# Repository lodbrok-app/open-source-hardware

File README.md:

# open-source-hardware
Open-source components of the Lodbrok stack

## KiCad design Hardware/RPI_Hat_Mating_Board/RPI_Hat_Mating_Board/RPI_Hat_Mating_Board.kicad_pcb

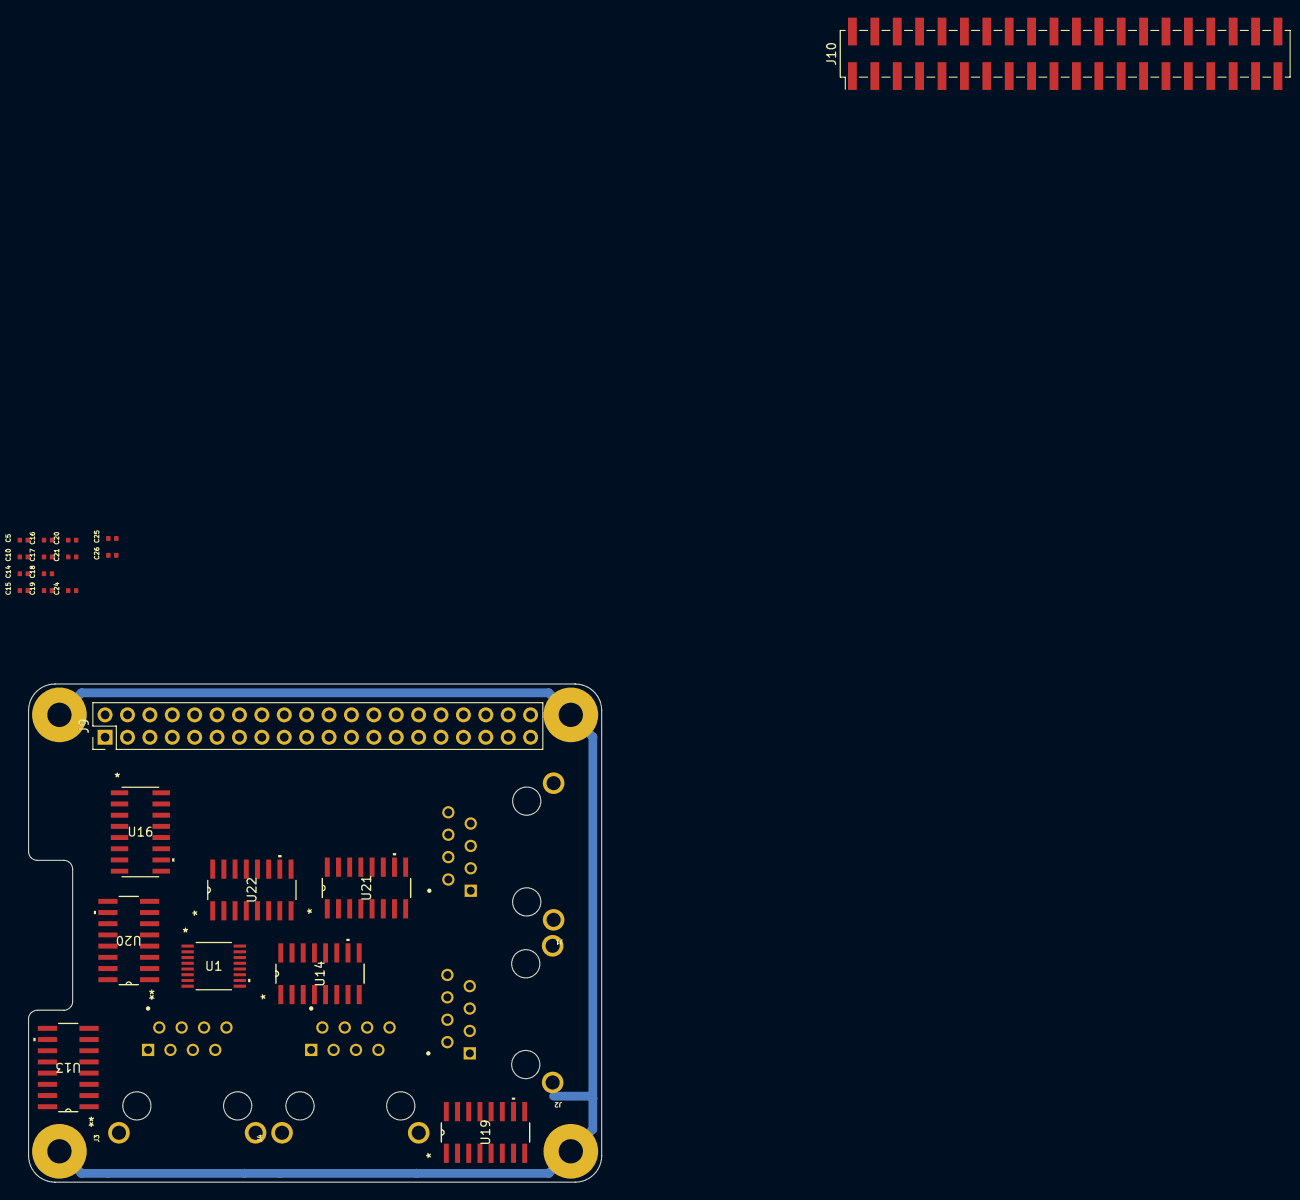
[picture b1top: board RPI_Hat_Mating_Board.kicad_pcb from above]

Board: 2 copper layers, 65.0 x 56.5 mm, 31 parts (0 on the bottom side), 48 nets.

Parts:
C5, C10, C14, C15, C16, C17, C18, C19, C20, C21, C24, C25, C26: Cap_0.1uF_10%_16V_0402; CAP_0402_0.6mm_Height
J1, J2, J3, J4: Conn_RJ45_Shielded_8p8c_RA_A-2004-2-4-LPS-N-R; A-2004-2-4-LPS-N-R
J9: Conn_02x20_Counter_Clockwise_MountingPin; PinHeader_2x20_P2.54mm_Vertical
J10: Conn_02x20_Counter_Clockwise_MountingPin; PinHeader_2x20_P2.54mm_Vertical_SMD
MP1, MP2, MP3, MP4: STAND_OFF_M3_2mm_NS_SMT; 9774020960
U1: TMUX1208PWR; PW_16_TEX
U13, U14: AM26LV32EIDR; D16
U16: 74HC137; SOIC16-N_MC_MCH
U19, U20, U21, U22: AM26LV31EIDR; D16

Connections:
3V3: C5.2, C10.2, C14.2, C15.2, C16.2, C17.2, C18.2, C19.2, C20.2, C21.2, C24.2, C25.2, C26.2, U1.2 (EN), U1.13 (VDD), U13.4 (G), U13.16 (VCC), U14.4 (G), U14.16 (VCC), U16.6 (E2), U16.16 (VCC), U19.4 (G), U19.16 (VCC), U20.4 (G), U20.16 (VCC), U21.4 (G), U21.16 (VCC), U22.4 (G), U22.16 (VCC)
5V0: J1.1, J2.1, J3.1, J4.1
/CS_1: U16.15 (~Y0), U19.1 (1A)
/CS_2: U16.14 (~Y1), U19.7 (2A)
/CS_3: U16.13 (~Y2), U19.9 (3A)
/CS_4: U16.12 (~Y3), U19.15 (4A)
/CS_5: U16.11 (~Y4), U20.1 (1A)
/CS_6: U16.10 (~Y5), U20.7 (2A)
/CS_7: U16.9 (~Y6), U20.9 (3A)
/CS_8: U16.7 (~Y7), U20.15 (4A)
/CS_DIFF_N_1: J1.3, U19.3 (1Z)
/CS_DIFF_N_2: J2.3, U19.5 (2Z)
/CS_DIFF_N_3: J3.3, U19.11 (3Z)
/CS_DIFF_N_4: J4.3, U19.13 (4Z)
/CS_DIFF_P_1: J1.6, U19.2 (1Y)
/CS_DIFF_P_2: J2.6, U19.6 (2Y)
/CS_DIFF_P_3: J3.6, U19.10 (3Y)
/CS_DIFF_P_4: J4.6, U19.14 (4Y)
/S0: U1.1 (A0), U16.1 (A0)
/S1: U1.16 (A1), U16.2 (A1)
/S2: U1.15 (A2), U16.3 (A2)
/SCLK: U21.1 (1A), U21.7 (2A), U21.9 (3A), U21.15 (4A), U22.1 (1A), U22.7 (2A), U22.9 (3A), U22.15 (4A)
/SCLK_DIFF_N_1: J1.5, U21.3 (1Z)
/SCLK_DIFF_N_2: J2.5, U21.5 (2Z)
/SCLK_DIFF_N_3: J3.5, U21.11 (3Z)
/SCLK_DIFF_N_4: J4.5, U21.13 (4Z)
/SCLK_DIFF_P_1: J1.4, U21.2 (1Y)
/SCLK_DIFF_P_2: J2.4, U21.6 (2Y)
/SCLK_DIFF_P_3: J3.4, U21.10 (3Y)
/SCLK_DIFF_P_4: J4.4, U21.14 (4Y)
/SDATA_1: U1.4 (S1), U13.3 (1Y)
/SDATA_2: U1.5 (S2), U13.5 (2Y)
/SDATA_3: U1.6 (S3), U13.11 (3Y)
/SDATA_4: U1.7 (S4), U13.13 (4Y)
/SDATA_5: U1.12 (S5), U14.3 (1Y)
/SDATA_6: U1.11 (S6), U14.5 (2Y)
/SDATA_7: U1.10 (S7), U14.11 (3Y)
/SDATA_8: U1.9 (S8), U14.13 (4Y)
/SDATA_DIFF_N_1: J1.8, U13.1 (1B)
/SDATA_DIFF_N_2: J2.8, U13.7 (2B)
/SDATA_DIFF_N_3: J3.8, U13.9 (3B)
/SDATA_DIFF_N_4: J4.8, U13.15 (4B)
/SDATA_DIFF_P_1: J1.7, U13.2 (1A)
/SDATA_DIFF_P_2: J2.7, U13.6 (2A)
/SDATA_DIFF_P_3: J3.7, U13.10 (3A)
/SDATA_DIFF_P_4: J4.7, U13.14 (4A)
CH_GND: J1.9 (MNT_1), J1.10 (MNT_2), J2.9 (MNT_1), J2.10 (MNT_2), J3.9 (MNT_1), J3.10 (MNT_2), J4.9 (MNT_1), J4.10 (MNT_2), MP1.1 (1_1), MP2.1 (1_1), MP3.1 (1_1), MP4.1 (1_1)
GND: C5.1, C10.1, C14.1, C15.1, C16.1, C17.1, C18.1, C19.1, C20.1, C21.1, C24.1, C25.1, C26.1, J1.2, J2.2, J3.2, J4.2, U1.14 (GND), U13.8 (GND), U13.12 (*G), U14.8 (GND), U14.12 (*G), U16.4 (~LE), U16.5 (~E1), U16.8 (GND), U19.8 (GND), U19.12 (*G), U20.8 (GND), U20.12 (*G), U21.8 (GND), U21.12 (*G), U22.8 (GND), U22.12 (*G)

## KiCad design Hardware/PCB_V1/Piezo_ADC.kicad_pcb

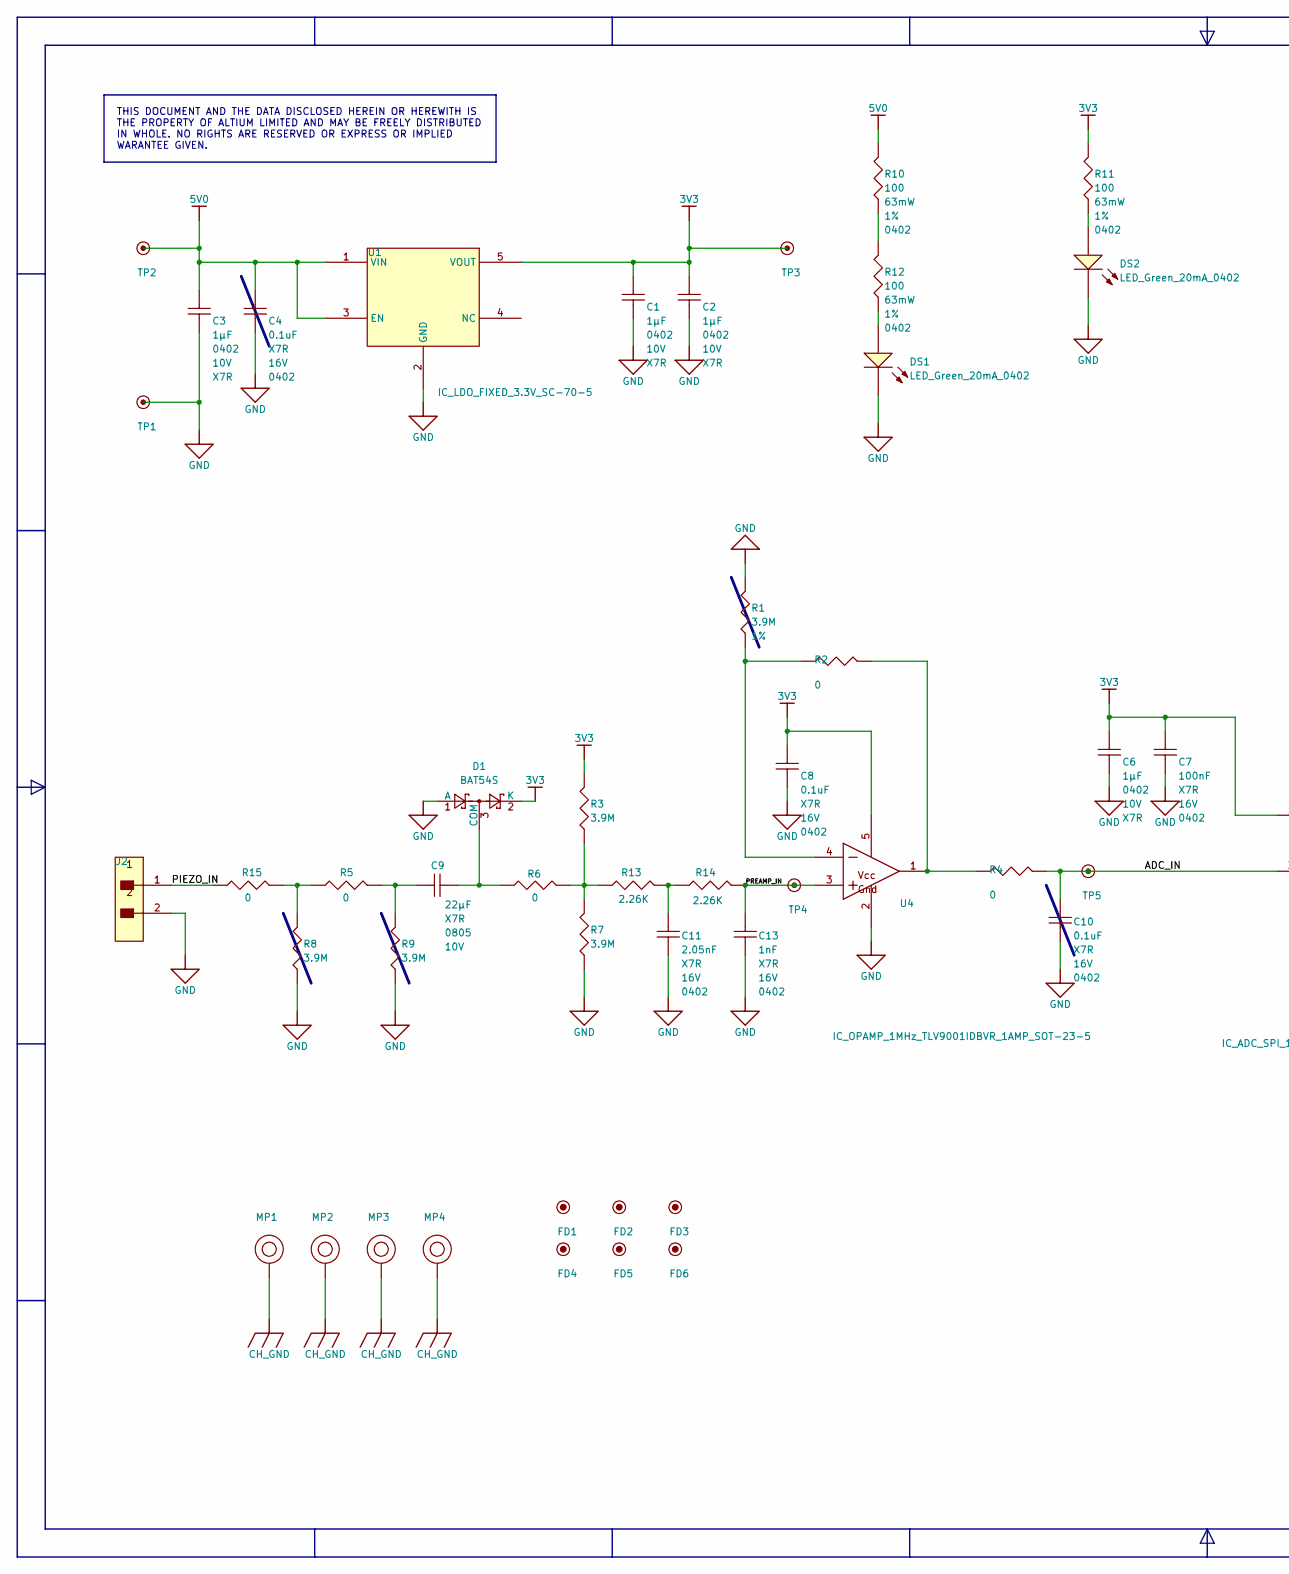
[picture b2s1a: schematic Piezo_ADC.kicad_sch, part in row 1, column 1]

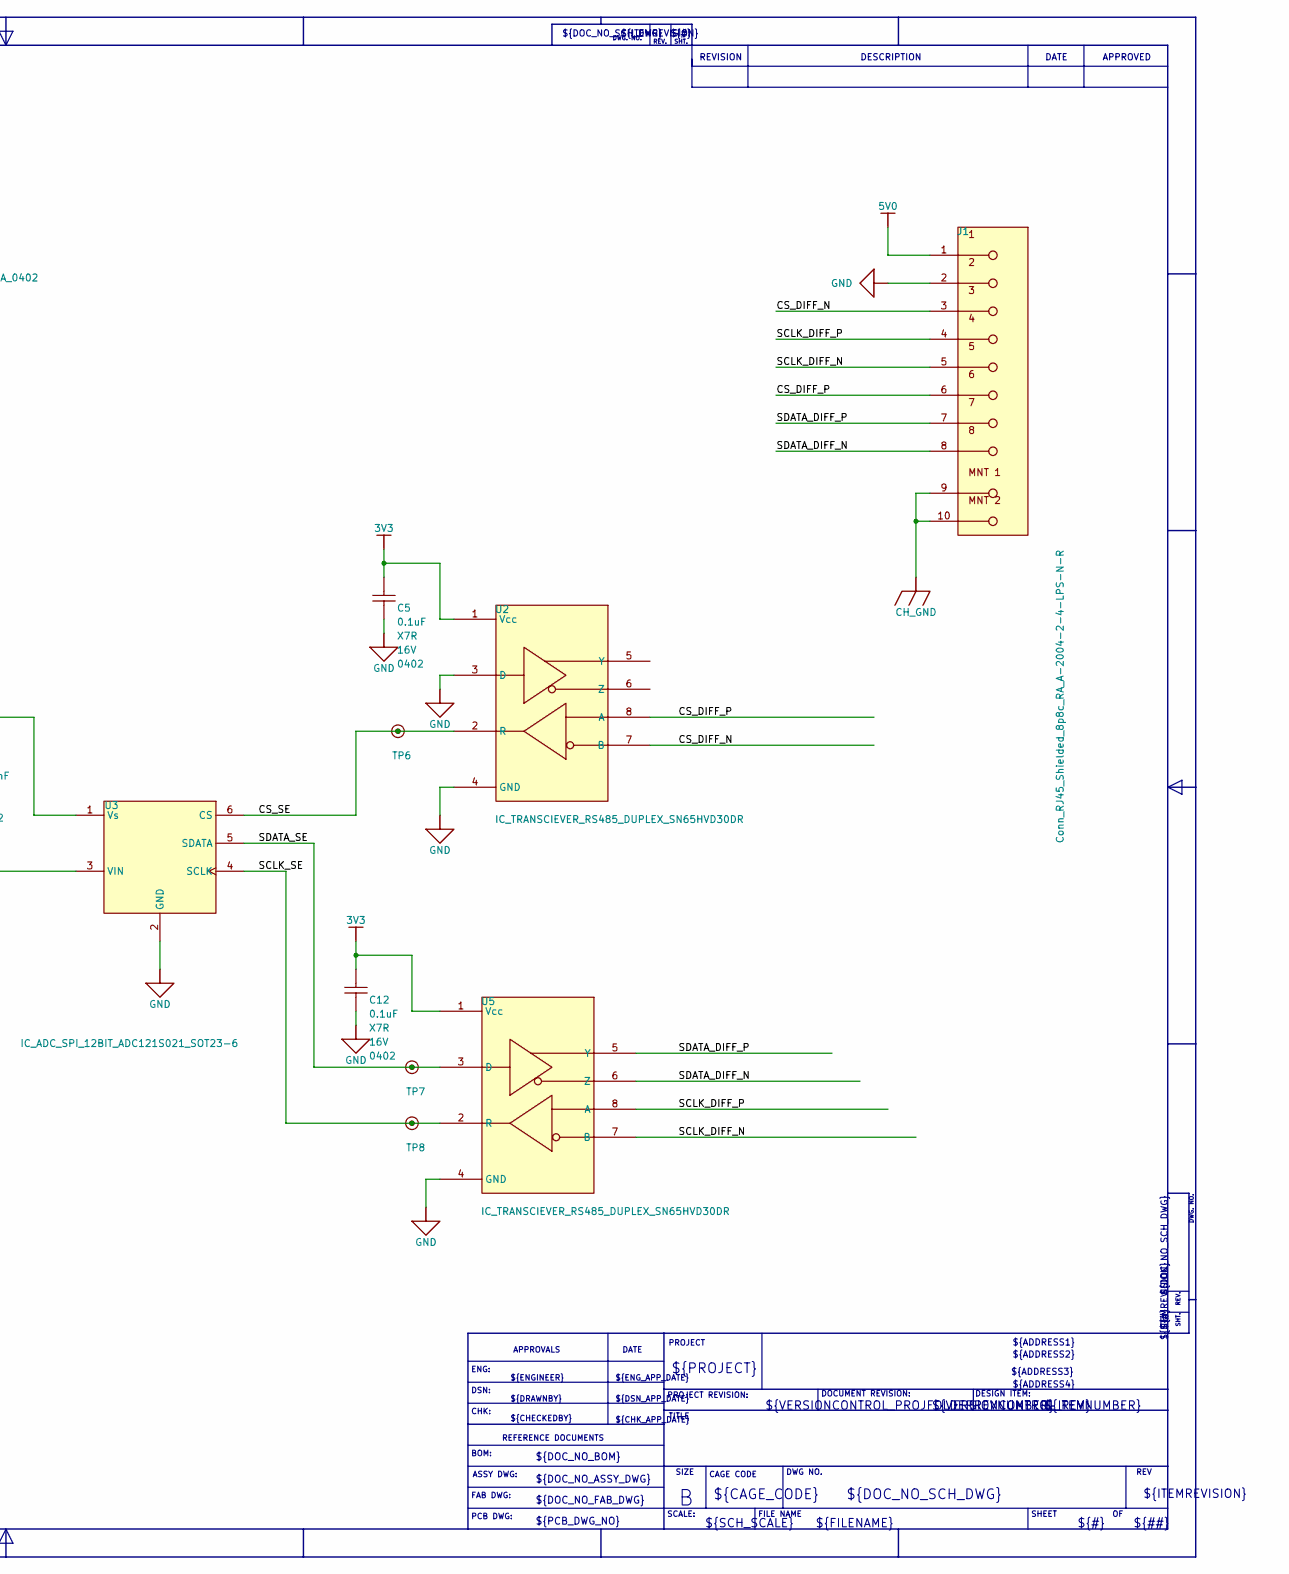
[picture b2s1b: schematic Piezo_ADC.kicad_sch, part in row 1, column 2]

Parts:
C1, C2, C3, C6: Cap_1uF_10%_10V_0402; CAP_0402_0.6mm_Height; VOLTAGE RATING 10V; TOLERANCE 10%
C4, C5, C7, C8, C10, C12: Cap_0.1uF_10%_16V_0402; CAP_0402_0.6mm_Height; TOLERANCE 10%; VOLTAGE RATING 16V
C9: Cap_22uF_20%_10V_0805; CAP_0805_1.45mm_Height; TOLERANCE 20%; VOLTAGE RATING 10V
C11: Cap_2.05nF_10%_16V_0402; CAP_0402_0.6mm_Height; TOLERANCE 10%; VOLTAGE RATING 16V
C13: Cap_1nF_10%_16V_0402; CAP_0402_0.6mm_Height; TOLERANCE 10%; VOLTAGE RATING 16V
D1: BAT54S; SOT-23
DS1, DS2: LED_Green_20mA_0402; LED_0402_Green_KA; FORWARD VOLTAGE 2.1V
FD1, FD2, FD3, FD4, FD5, FD6: FID1X2R
J1: Conn_RJ45_Shielded_8p8c_RA_A-2004-2-4-LPS-N-R; A-2004-2-4-LPS-N-R; VOLTAGE RATING 150V
J2: Conn_2Pos_3.96mm_1Row_TH_JST_B2PS-VH; JST_B2PS-VH-FP; VOLTAGE RATING 250V; MPN1 B2PS-VH
MP1, MP2, MP3, MP4: STAND_OFF_M3_2mm_NS_SMT; 9774020960
R1: Res_3M9_1%_63mW_0402; RES_0402; TOLERANCE 1%; VOLTAGE RATING 50V
R2, R4, R5, R6, R15: Res_0R0_1%_63mW_0402; RES_0402; VOLTAGE RATING 50V
R3, R7, R8, R9: Res_3M9_1%_63mW_0402; RES_0402; VOLTAGE RATING 50V
R10, R11, R12: Res_100R_1%_63mW_0402; RES_0402; TOLERANCE 1%; VOLTAGE RATING 50V
R13, R14: Res_2.26kR0_1%_63mW_0402; RES_0402; VOLTAGE RATING 50V
TP1, TP3, TP5, TP6, TP7, TP8: TPAD6R; Keystone 5001 TP
TP2, TP4: TPAD6R; TP06R
U1: IC_LDO_FIXED_3.3V_SC-70-5; SOT23-5; OUTPUT VOLTAGE 3.3V; DROPOUT VOLTAGE 310mV
U2, U5: IC_TRANSCIEVER_RS485_DUPLEX_SN65HVD30DR; SOIC-8
U3: IC_ADC_SPI_12BIT_ADC121S021_SOT23-6; SOT-23-6
U4: IC_OPAMP_1MHz_TLV9001IDBVR_1AMP_SOT-23-5; SOT23-5; MPN1 TLV9001IDBVR

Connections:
3V3: C1.2, C2.2, C5.2, C6.2, C7.2, C8.2, C12.2, D1.2 (K), R3.2, R11.2, TP3.1 (TP_1), U1.5 (VOUT), U2.1 (Vcc), U3.1 (Vs), U4.5 (Vcc), U5.1 (Vcc)
5V0: C3.2, C4.2, J1.1, R10.2, TP2.1 (TP_1), U1.1 (VIN), U1.3 (EN)
/ADC_IN: C10.1, R4.2, TP5.1 (TP_1), U3.3 (VIN)
/CS_DIFF_N: J1.3, U2.7 (B)
/CS_DIFF_P: J1.6, U2.8 (A)
/CS_SE: TP6.1 (TP_1), U2.2 (R), U3.6 (CS)
/PIEZO_IN: J2.1, R15.1
/PREAMP_IN: C13.1, R14.2, TP4.1 (TP_1), U4.3 (+IN)
/SCLK_DIFF_N: J1.5, U5.7 (B)
/SCLK_DIFF_P: J1.4, U5.8 (A)
/SCLK_SE: TP8.1 (TP_1), U3.4 (SCLK), U5.2 (R)
/SDATA_DIFF_N: J1.8, U5.6 (Z)
/SDATA_DIFF_P: J1.7, U5.5 (Y)
/SDATA_SE: TP7.1 (TP_1), U3.5 (SDATA), U5.3 (D)
CH_GND: J1.9 (MNT_1), J1.10 (MNT_2), MP1.1 (1_1), MP2.1 (1_1), MP3.1 (1_1), MP4.1 (1_1)
GND: C1.1, C2.1, C3.1, C4.1, C5.1, C6.1, C7.1, C8.1, C10.2, C11.2, C12.1, C13.2, D1.1 (A), DS1.2 (K), DS2.2 (K), J1.2, J2.2, R1.2, R7.1, R8.1, R9.1, TP1.1 (TP_1), U1.2 (GND), U2.3 (D), U2.4 (GND), U3.2 (GND), U4.2 (GND), U5.4 (GND)
unnamed: C9.1, R5.2, R9.2
unnamed: C11.1, R13.2, R14.1
unnamed: C9.2, D1.3 (COM), R6.1
unnamed: DS1.1 (A), R12.1
unnamed: DS2.1 (A), R11.1
unnamed: R10.1, R12.2
unnamed: R3.1, R6.2, R7.2, R13.1
unnamed: R5.1, R8.2, R15.2
unnamed: R1.1, R2.1, U4.4 (-IN)
unnamed: R2.2, R4.1, U4.1 (OUT)

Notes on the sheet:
DESCRIPTION
${DOC_NO_SCH_DWG}
${CHK_APP_DATE}
SHT.
APPROVED
PCB DWG:
PROJECT
${#}
DWG NO.
REV
${VERSIONCONTROL_PROJFOLDERREVNUMBER}
${ADDRESS1}
FILE NAME
${ITEMREVISION}
DWG. NO.
${ENGINEER}
DESIGN ITEM:
REFERENCE DOCUMENTS
DATE
REV.
${##}
ENG:
APPROVALS
${CHECKEDBY}
${CAGE_CODE}
FAB DWG:
TITLE
SHEET
${DOC_NO_FAB_DWG}
SCALE:
${DSN_APP_DATE}
CHK:
${VERSIONCONTROL_REVNUMBER}
${TITLE}
SIZE
${PROJECT}
DSN:
PROJECT REVISION:
${PCB_DWG_NO}
CAGE CODE

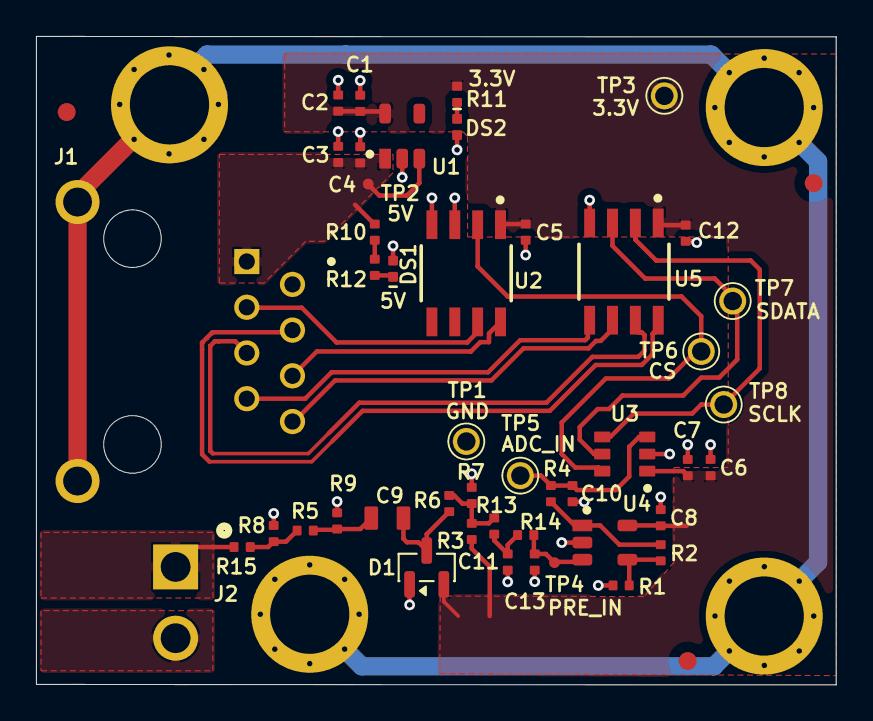
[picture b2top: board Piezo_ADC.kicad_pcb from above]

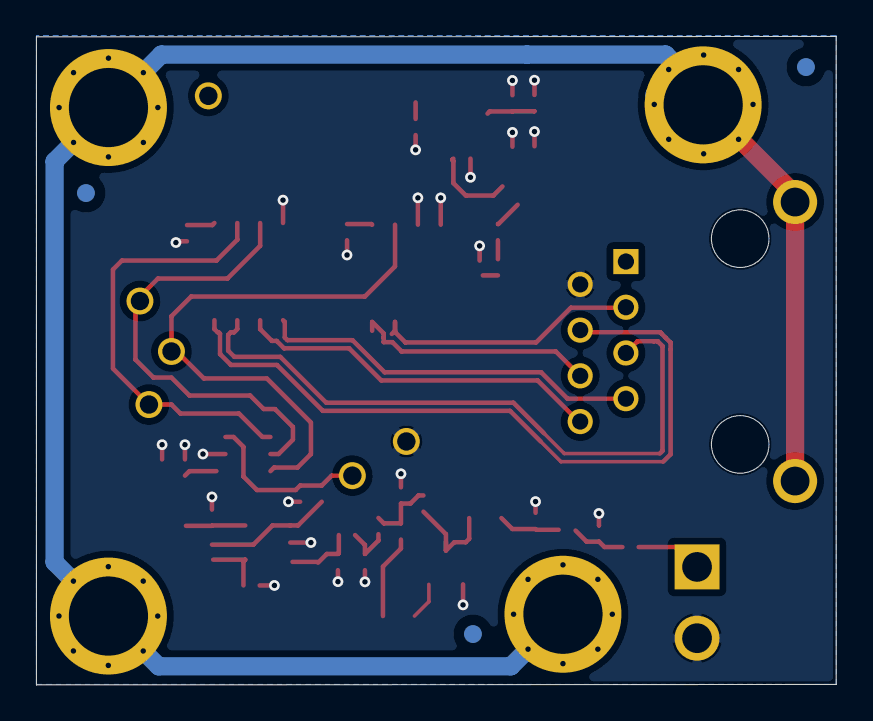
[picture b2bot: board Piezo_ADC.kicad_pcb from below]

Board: 2 copper layers, 44.4 x 36.0 mm, 56 parts (7 on the bottom side), 26 nets.

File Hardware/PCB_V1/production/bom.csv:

Designator,Footprint,Quantity,Value,LCSC Part #
"C1, C2, C3, C6",CAP_0402_0.6mm_Height,4,Cap_1uF_10%_10V_0402,
"C10, C12, C4, C5, C7, C8",CAP_0402_0.6mm_Height,6,Cap_0.1uF_10%_16V_0402,
C11,CAP_0402_0.6mm_Height,1,Cap_2.05nF_10%_16V_0402,
C13,CAP_0402_0.6mm_Height,1,Cap_1nF_10%_16V_0402,
C9,CAP_0805_1.45mm_Height,1,Cap_22uF_20%_10V_0805,
D1,SOT-23,1,BAT54S,
"DS1, DS2",LED_0402_Green_KA,2,LED_Green_20mA_0402,
"FD1, FD2, FD3, FD4, FD5, FD6",FID1X2R,6,FID1X2R,
J1,A-2004-2-4-LPS-N-R,1,Conn_RJ45_Shielded_8p8c_RA_A-2004-2-4-LPS-N-R,
J2,JST_B2PS-VH-FP,1,Conn_2Pos_3.96mm_1Row_TH_JST_B2PS-VH,
"MP1, MP2, MP3, MP4",9774020960,4,STAND_OFF_M3_2mm_NS_SMT,
"R1, R3, R7, R8, R9",RES_0402,5,Res_3M9_1%_63mW_0402,
"R10, R11, R12",RES_0402,3,Res_100R_1%_63mW_0402,
"R13, R14",RES_0402,2,Res_2.26kR0_1%_63mW_0402,
"R15, R2, R4, R5, R6",RES_0402,5,Res_0R0_1%_63mW_0402,
"TP1, TP3, TP5, TP6, TP7, TP8",Keystone 5001 TP,6,TPAD6R,
"TP2, TP4",TP06R,2,TPAD6R,
U1,SOT23-5,1,IC_LDO_FIXED_3.3V_SC-70-5,
"U2, U5",SOIC-8,2,IC_TRANSCIEVER_RS485_DUPLEX_SN65HVD30DR,
U3,SOT-23-6,1,IC_ADC_SPI_12BIT_ADC121S021_SOT23-6,
U4,SOT23-5,1,IC_OPAMP_1MHz_TLV9001IDBVR_1AMP_SOT-23-5,
